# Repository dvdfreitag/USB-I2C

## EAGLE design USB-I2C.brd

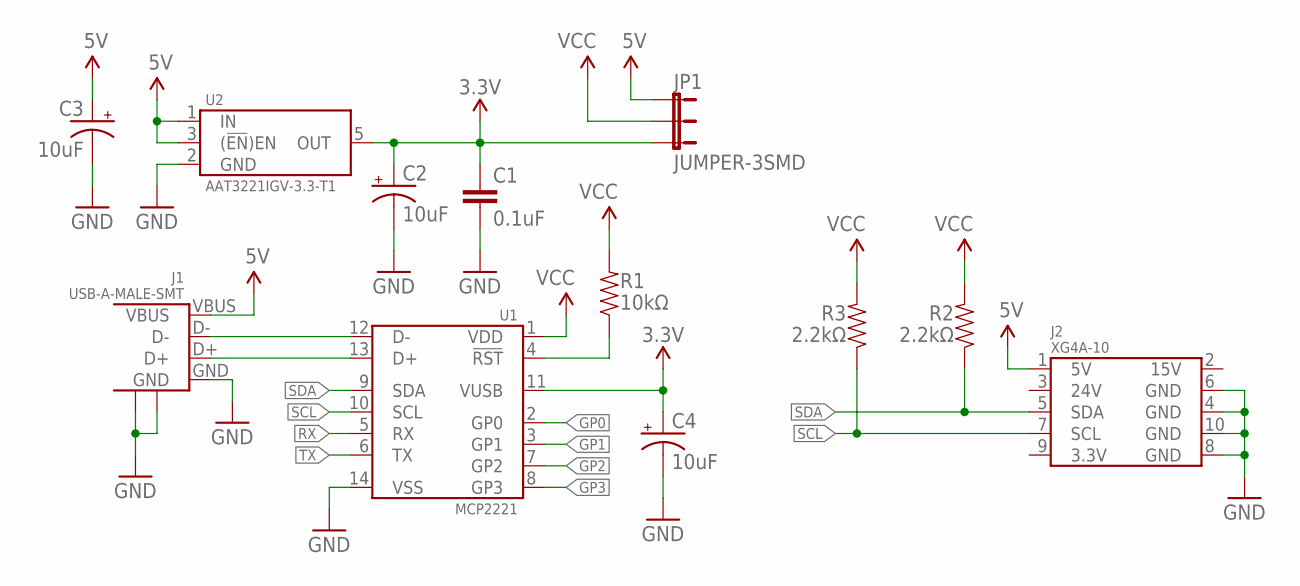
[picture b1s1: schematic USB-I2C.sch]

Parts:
C1: 0.1uF; 0805-CAP
C2, C3, C4: 10uF; 0805-CAP_POL
J1: USB-A-MALE-SMT
J2: XG4A-10; M05X2_SHROUD
JP1: JUMPER-3SMD; SJ_3
R1: 10kΩ; 0805-RES
R2, R3: 2.2kΩ; 0805-RES
U1: MCP2221; SOIC-14
U2: AAT3221IGV-3.3-T1; SOT23-5

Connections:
3.3V: C1.1, C2.A (+), C4.A (+), JP1.3, U1.11 (VUSB), U2.5 (OUT)
5V: C3.A (+), J1.VBUS, J2.1 (5V), JP1.1, U2.1 (IN), U2.3 ((!EN!)EN)
D_N: J1.D-, U1.12 (D-)
D_P: J1.D+, U1.13 (D+)
GND: C1.2, C2.C (-), C3.C (-), C4.C (-), J1.GND, J1.P$1, J1.P$3, J2.4 (GND), J2.6 (GND), J2.8 (GND), J2.10 (GND), U1.14 (VSS), U2.2 (GND)
GP0: U1.2 (GP0)
GP1: U1.3 (GP1)
GP2: U1.7 (GP2)
GP3: U1.8 (GP3)
unnamed: R1.1, U1.4 (!RST)
RX: U1.5 (RX)
SCL: J2.7 (SCL), R3.1, U1.10 (SCL)
SDA: J2.5 (SDA), R2.1, U1.9 (SDA)
TX: U1.6 (TX)
VCC: JP1.2, R1.2, R2.2, R3.2, U1.1 (VDD)

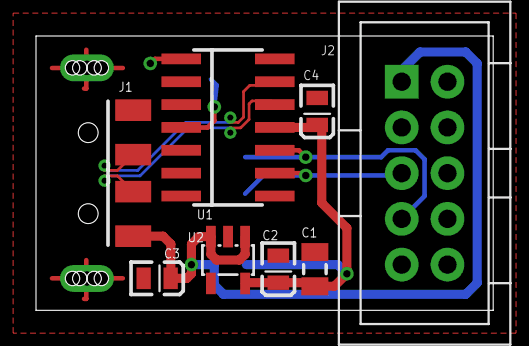
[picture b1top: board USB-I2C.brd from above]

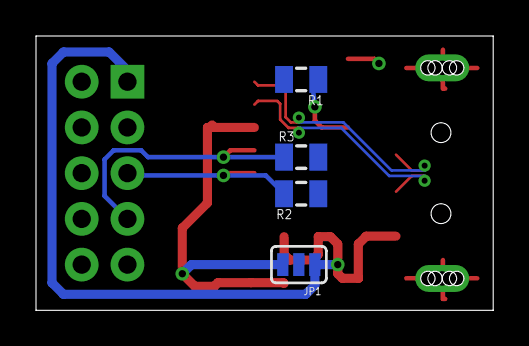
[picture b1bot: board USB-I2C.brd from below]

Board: 2 copper layers, 25.4 x 15.2 mm, 12 parts (4 on the bottom side), 9 nets.

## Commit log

2016-08-12 Create LICENSE

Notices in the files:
parts and their libraries:
SparkFun-Passives: Licensing: CC v3.0 Share-Alike You are welcome to use this library for commercial purposes.
